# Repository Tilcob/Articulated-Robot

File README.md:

# 3DOF Robotic Arm Controller (Arduino Nano)

## Overview

This project implements a 3DOF robotic arm controller using an Arduino Nano.
The system includes:

* Analytical forward and inverse kinematics
* Potentiometer-based Cartesian target input (X, Y, Z)
* Button-based target commit (short press)
* Long-press trajectory execution (predefined waypoints)
* Smooth joint motion control
* Configurable servo calibration and joint limits

The kinematic model is consistent with the following convention:

```
x =  cos(q1) * (L1 cos(q2) + L2 cos(q2+q3))
y = -sin(q1) * (L1 cos(q2) + L2 cos(q2+q3))
z =  h + L1 sin(q2) + L2 sin(q2+q3)
```

The negative sign in the Y coordinate is fixed and part of the model.

---

## Hardware Requirements

* Arduino Nano (ATmega328)
* 3 RC servos (Base, Shoulder, Elbow)
* Optional gripper servo
* 3 potentiometers (X, Y, Z)
* Optional gripper potentiometer
* 1 momentary push button
* External 5–6V servo power supply (recommended)

---

## Wiring

### Potentiometers

Each potentiometer:

* One side → 5V
* Other side → GND
* Middle pin → Analog input (A0–A3)

### Button

Configured with `INPUT_PULLUP`.

Wiring:

```
Pin 2  ---- Button ---- GND
```

* Not pressed → HIGH
* Pressed → LOW

### Servos

* Signal pins defined in `Config.h`
* Power servos from external supply
* Connect grounds together (Arduino GND ↔ Servo GND)

---

## Project Structure

* `Config.h` — geometry, limits, pins, calibration
* `Types.h` — basic data structures
* `Kinematics.*` — forward and inverse kinematics
* `Input.*` — potentiometer + button handling
* `Mapping.*` — joint angles → servo degrees
* `Motion.*` — smooth motion controller
* `Trajectory.*` — waypoint-based path execution
* `main.cpp` — system integration

---

## Operation Modes

### 1. Manual Target Mode (Short Button Press)

1. Adjust X, Y, Z using potentiometers.
2. Press the button briefly.
3. The target is latched and the arm moves to that position.

### 2. Trajectory Mode (Long Press > 700 ms)

1. Hold the button.
2. After release, trajectory execution begins.
3. The arm moves through predefined waypoints in `Trajectory.cpp`.

---

## Defining Custom Trajectories

Edit `Trajectory.cpp`:

```cpp
const Waypoint TRAJ_POINTS[] = {
    { {0.11f,  0.00f, 0.09f}, 0.5f },
    { {0.10f,  0.03f, 0.11f}, 0.5f },
    { {0.08f, -0.03f, 0.06f}, 0.2f }
};
```

Each waypoint contains:

* Cartesian position (meters)
* Gripper value (0.0–1.0)

---

## Motion Control

The motion controller:

* Limits joint speed (`MAX_SPEED_DEG_PER_S`)
* Moves joints smoothly toward targets
* Detects arrival within tolerance
* Advances trajectory automatically

---

## Calibration

Adjust in `Config.h`:

* `BASE_ZERO_DEG`
* `SHOULDER_ZERO_DEG`
* `ELBOW_ZERO_DEG`
* `*_SIGN`

Procedure:

1. Move arm mechanically to mathematical zero pose.
2. Set servo zero angles accordingly.
3. Adjust sign if joint moves in wrong direction.

---

## Inverse Kinematics

The IK uses a stable atan2-based solution:

```
q1 = atan2(-y, x)
q3 = atan2(±sqrt(1 - c3²), c3)
q2 = alpha - beta
```

Advantages:

* Stable near singularities
* Supports elbow-up and elbow-down configurations
* No acos flipping issues

---

## Safety Notes

* Always power servos from external supply.
* Avoid commanding unreachable targets.
* Ensure mechanical limits match software limits.

---

Serial Monitor: Permitted coordinates (depending on `h`, `L1`, `L2`)

Entries in the Serial Monitor are **absolute target points in the base coordinate system** in **metres**:

```
x y z [g]
```

* `x, y, z` in metres
* optional `g` as gripper value from `0.0 .. 1.0`

Relative TCP commands are also possible:

```
t dx dy dz [g]
```

Here, `(dx,dy,dz)` is specified in the current TCP coordinate system and is converted internally to the base system.

### Geometric conditions for valid targets

With

* `r = sqrt(x² + y²)`
* `d = sqrt(r² + (z - h)²)`

the following must apply:

* `R_MIN <= r <= R_MAX`
* `Z_MIN <= z <= Z_MAX`
* `|L1 - L2| <= d <= (L1 + L2)`

This is the combination of the configured cylindrical boundaries and the actual 2-link reachability.

### Current figures from `Config.h`

* `L1 = 0.080 m`
* `L2 = 0.068 m`
* `h  = 0.027 m`
* `R_MIN = 0.050 m`
* `R_MAX = L1 + L2 = 0.148 m`
* `Z_MIN = h - 0.02 = 0.007 m`
* `Z_MAX = h + 0.80*(L1+L2) = 0.1454 m`
* Additional IK ring: `0.012 m <= d <= 0.148 m`

### Examples of permitted entries

* `0.10 0.00 0.08`
* `0.09 0.03 0.11 0.6`
* `t 0.01 0.00 -0.01`

If a target is outside the workspace, the firmware reports `WS ERR` or `IK ERR`.

---

## Future Improvements

Possible extensions:

* Cartesian linear interpolation between waypoints
* Trapezoidal acceleration profiles
* Closed-loop control with encoders
* Serial command interface (G-code style)

---

## License

Personal educational project.

---

Developed for Arduino Nano 3DOF robotic arm experimentation.

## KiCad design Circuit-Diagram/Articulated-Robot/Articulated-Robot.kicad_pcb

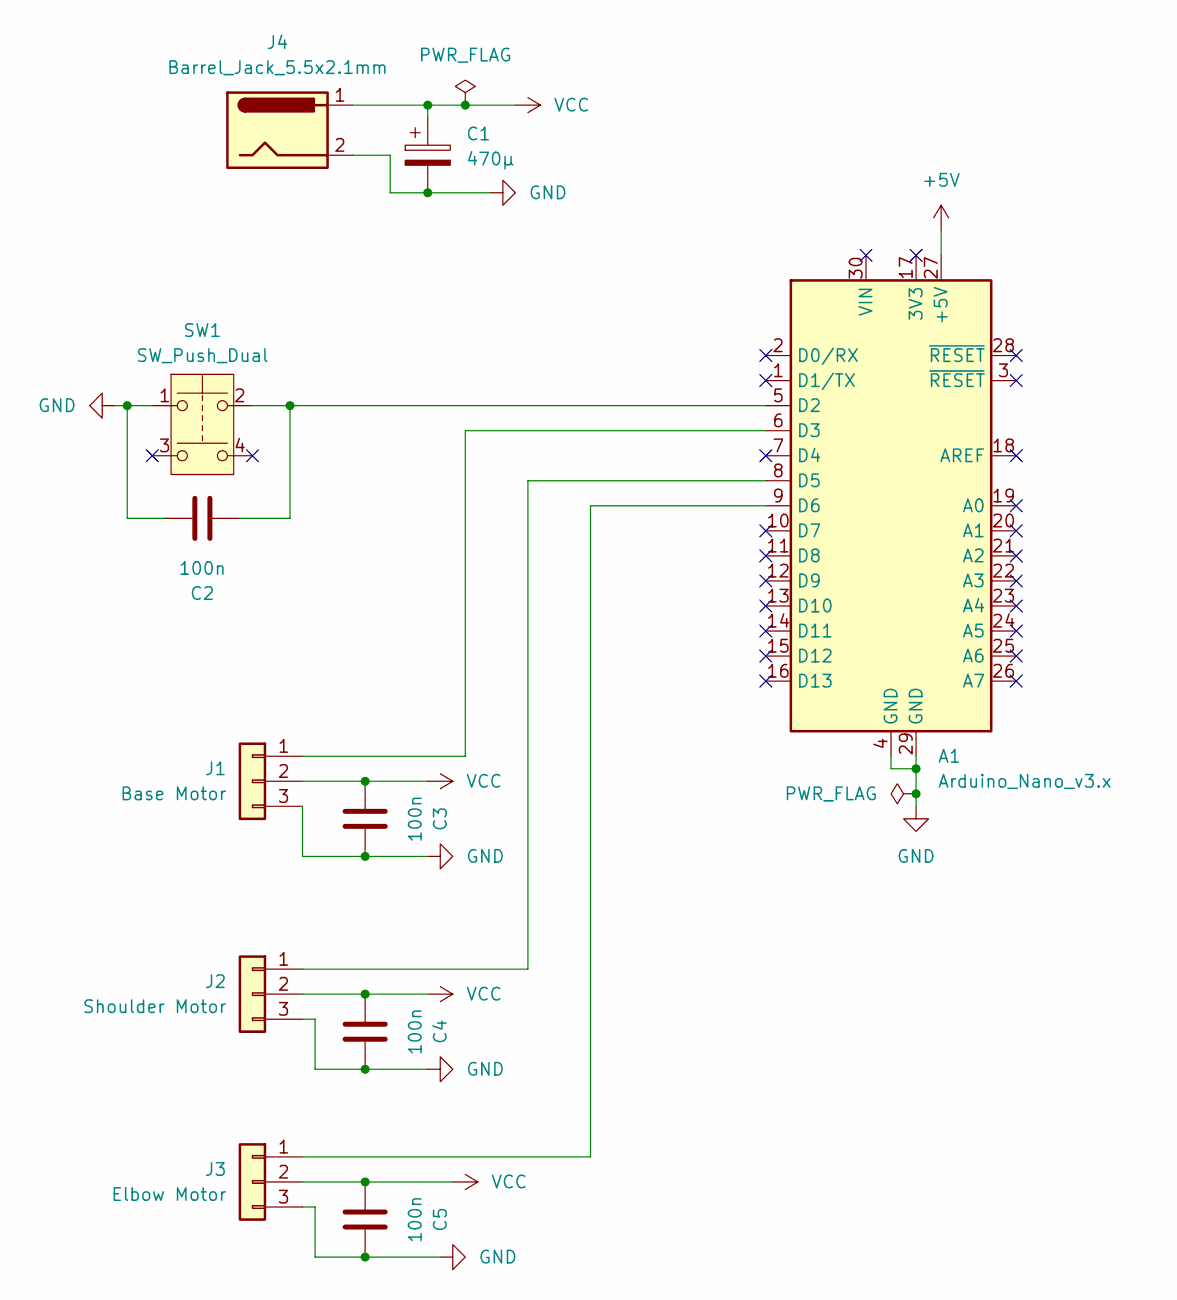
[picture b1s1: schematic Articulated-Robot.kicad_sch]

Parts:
A1: Arduino_Nano_v3.x; Arduino_Nano_WithMountingHoles
C1: 470µ; CP_Radial_D6.3mm_P2.50mm
C2, C3, C4, C5: 100n; C_Disc_D4.3mm_W1.9mm_P5.00mm
J1: Base Motor; PinHeader_1x03_P2.54mm_Vertical
J2: Shoulder Motor; PinHeader_1x03_P2.54mm_Vertical
J3: Elbow Motor; PinHeader_1x03_P2.54mm_Vertical
J4: Barrel_Jack_5.5x2.1mm
SW1: SW_Push_Dual; SW_PUSH_6mm_H4.3mm

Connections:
+5V: A1.27 (+5V)
GND: A1.4 (GND), A1.29 (GND), C1.2, C2.1, C3.1, C4.1, C5.1, J1.3, J2.3, J3.3, J4.2, SW1.1
unnamed: A1.5 (D2), C2.2, SW1.2
unnamed: A1.6 (D3), J1.1
unnamed: A1.8 (D5), J2.1
unnamed: A1.9 (D6), J3.1
VCC: C1.1, C3.2, C4.2, C5.2, J1.2, J2.2, J3.2, J4.1

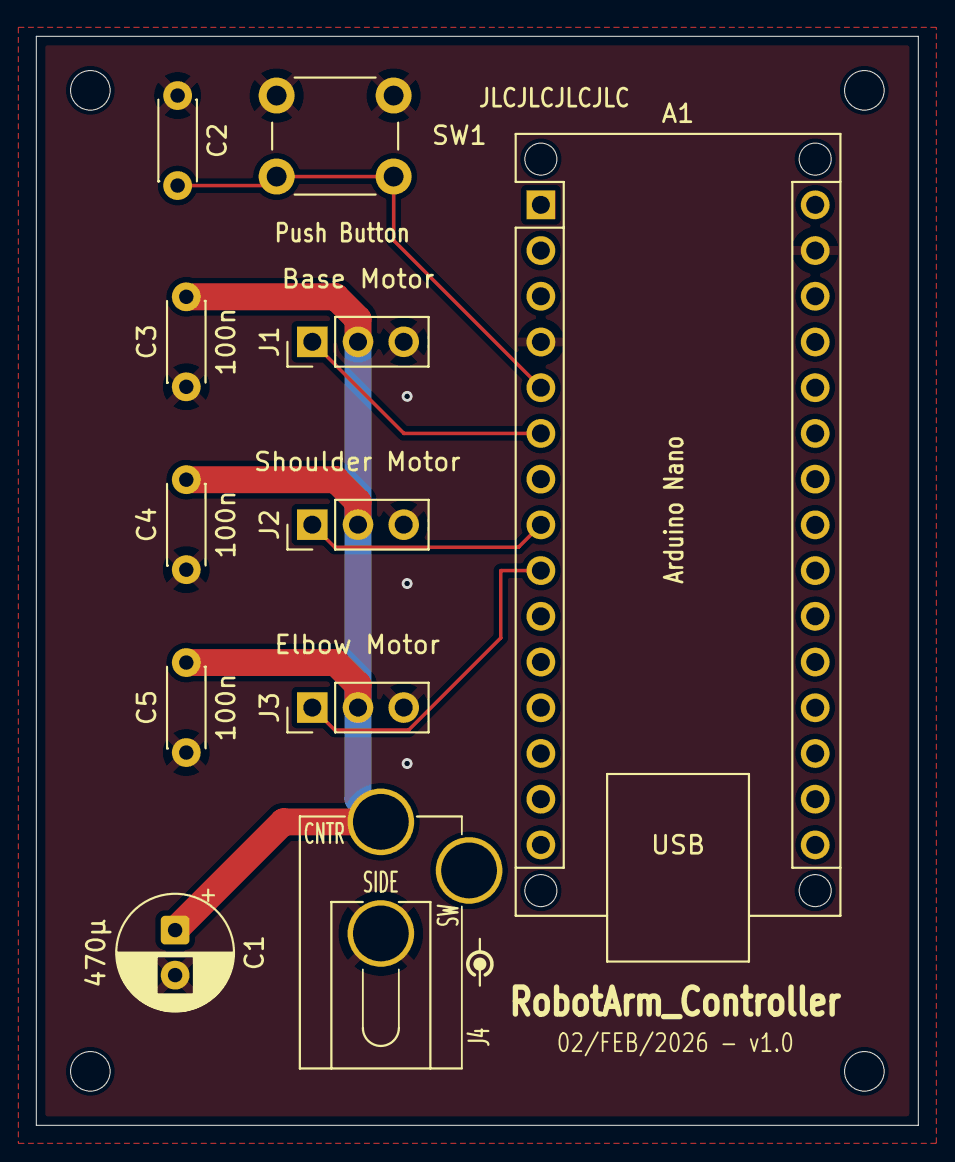
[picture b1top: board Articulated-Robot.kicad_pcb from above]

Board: 2 copper layers, 49.0 x 60.5 mm, 11 parts (0 on the bottom side), 6 nets.

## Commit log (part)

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2026-02-13 Updated the kinematics to the calculated angles and positions.
2026-02-13 Updated the poti input to be better.
2026-02-13 Added a trajectory to follow a path.
2026-02-13 Add README for 3DOF Robotic Arm Controller
    Added comprehensive documentation for the 3DOF robotic arm controller project, including hardware requirements, wiring instructions, project structure, operation modes, and safety notes.
2026-02-13 Renamed to better variable names.
2026-02-13 Made the cad for the robot
2026-02-14 Added KiCad and fixed the q3 bug.
2026-02-14 Added debug code.
2026-02-14 Fixed the mapping bug.
2026-02-15 Made and ordered a pcb for the circuit.
2026-02-16 Made some minor adjustments to the motion controller and added a new function to clamp floats.
2026-02-16 Refactored code for better organization and readability.
2026-02-16 Made the trajectory class more efficient and added a new function to clamp floats.
2026-02-16 Changed trajectory points to be in the workspace of the robot.
2026-02-16 Optimized trajectory points, added calibration mode, and improved servo saturation handling.
2026-02-16 Refactored some code.
2026-02-16 Refactored code to improve organization, added `Workspace` class for clamping functionality, separated trajectory data into its own file, and extended serial control capabilities.
2026-02-16 Fixed the z clamp bug by clamping z coordinates and ensuring reach distance is within bounds.
